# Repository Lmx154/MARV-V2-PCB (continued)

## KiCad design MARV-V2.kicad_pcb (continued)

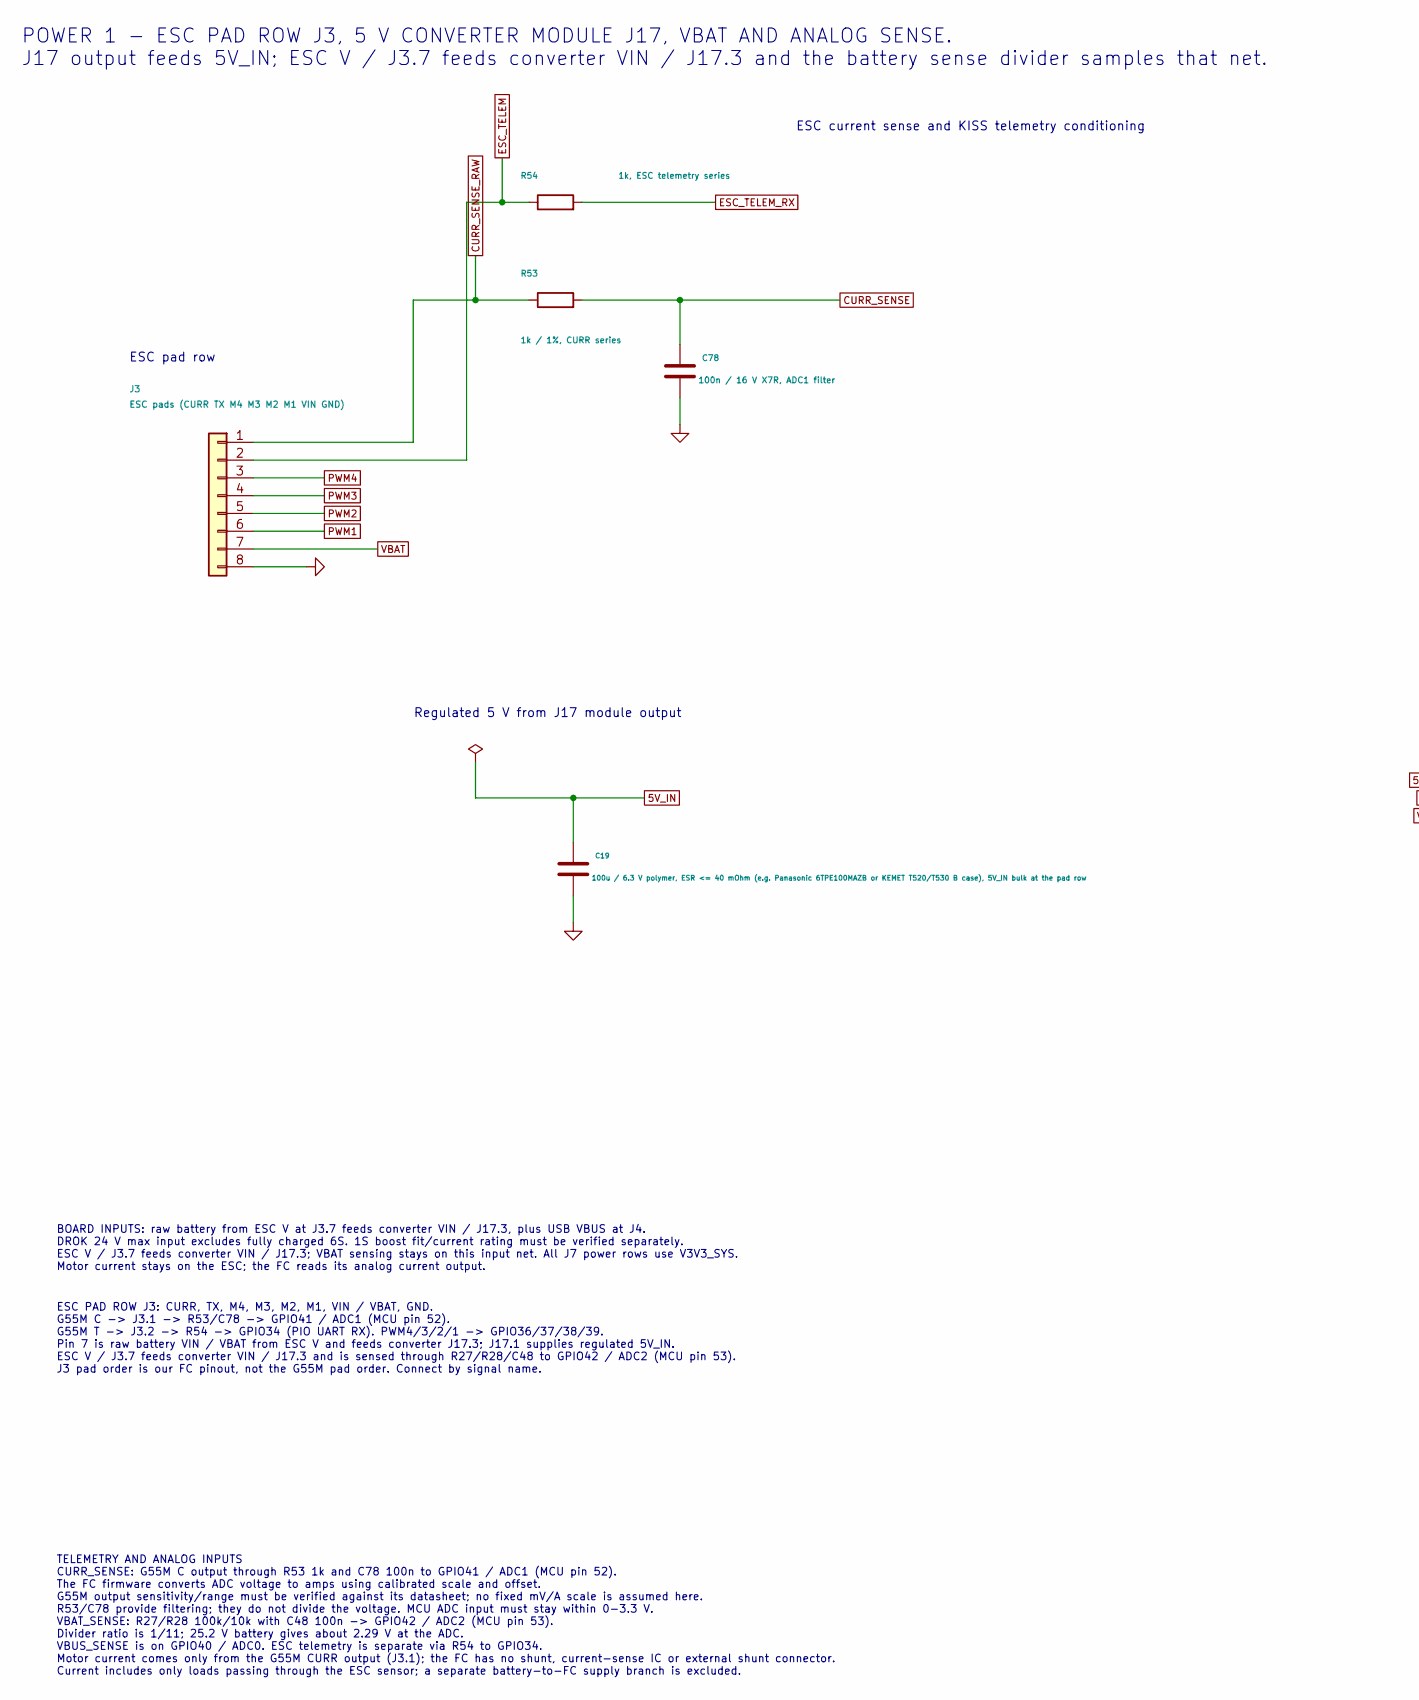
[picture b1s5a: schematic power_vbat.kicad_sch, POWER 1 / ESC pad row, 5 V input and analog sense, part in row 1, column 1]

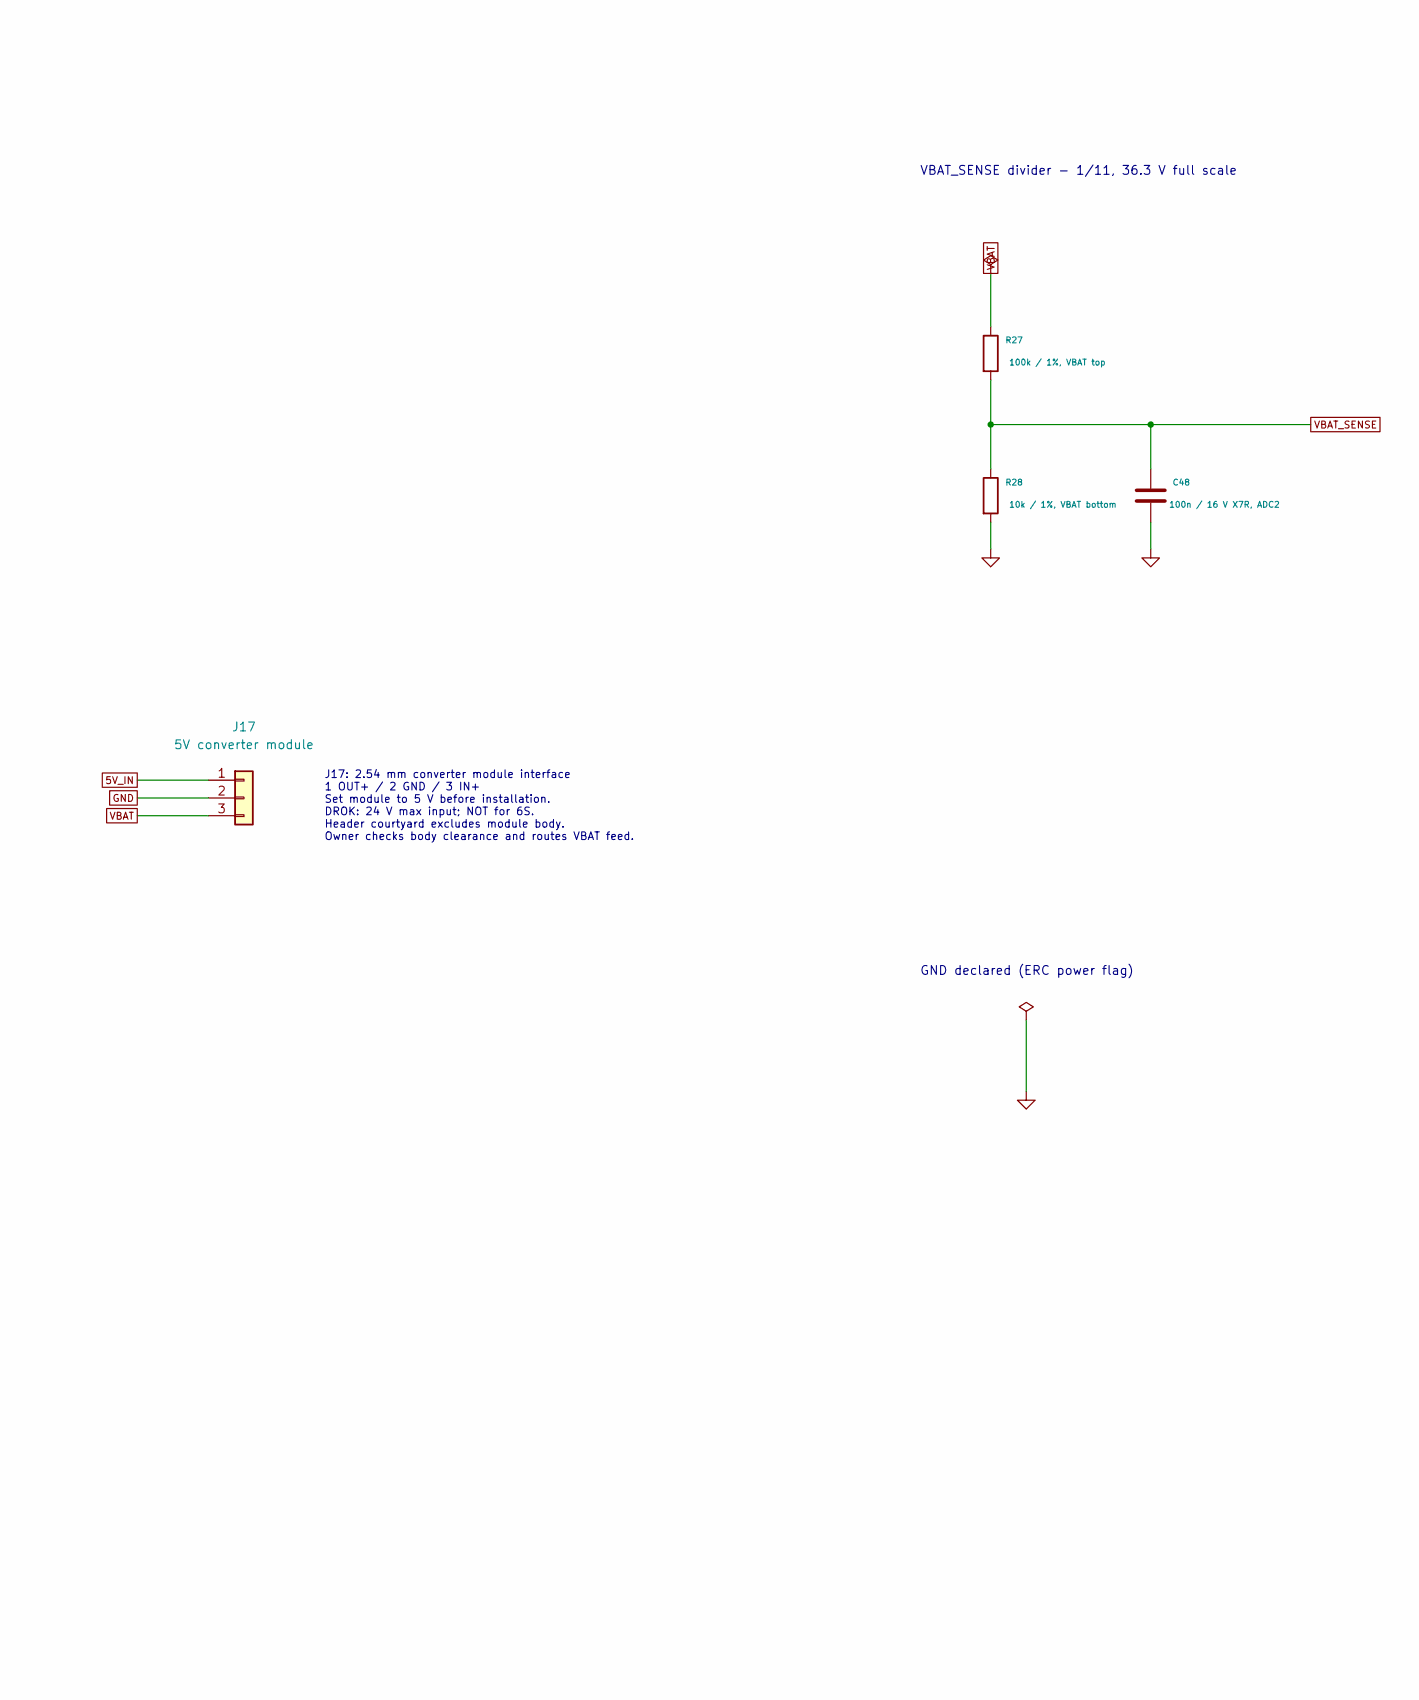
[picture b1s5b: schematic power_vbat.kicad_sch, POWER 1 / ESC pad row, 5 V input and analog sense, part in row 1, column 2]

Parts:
C19: 100u / 6.3 V polymer, ESR <= 40 mOhm (e.g. Panaso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; CP_EIA-3528-21_Kemet-B; LCSC C79109
C48: 100n / 16 V X7R, ADC2; C_0402_1005Metric; LCSC C1525
C78: 100n / 16 V X7R, ADC1 filter; C_0402_1005Metric; LCSC C1525
J3: ESC pads (CURR TX M4 M3 M2 M1 VIN GND); PadRow_1x08_P2.00mm
J17: 5V converter module; PinHeader_1x03_P2.54mm_Vertical
R27: 100k / 1%, VBAT top; R_0402_1005Metric; LCSC C25741
R28: 10k / 1%, VBAT bottom; R_0402_1005Metric; LCSC C25744
R53: 1k / 1%, CURR series; R_0402_1005Metric; LCSC C11702
R54: 1k, ESC telemetry series; R_0402_1005Metric; LCSC C11702

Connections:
5V_IN: C19.1, J17.1; also elsewhere on the board
CURR_SENSE: C78.1, R53.2; also elsewhere on the board
CURR_SENSE_RAW: J3.1, R53.1
ESC_TELEM: J3.2, R54.1
ESC_TELEM_RX: R54.2; also elsewhere on the board
GND: C19.2, C48.2, C78.2, J3.8, J17.2, R28.2; also elsewhere on the board
PWM1: J3.6; also elsewhere on the board
PWM2: J3.5; also elsewhere on the board
PWM3: J3.4; also elsewhere on the board
PWM4: J3.3; also elsewhere on the board
VBAT: J3.7, J17.3, R27.1
VBAT_SENSE: C48.1, R27.2, R28.1; also elsewhere on the board

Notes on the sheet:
ESC PAD ROW J3: CURR, TX, M4, M3, M2, M1, VIN / VBAT, GND. G55M C -> J3.1 -> R53/C78 -> GPIO41 / ADC1 (MCU pin 52). G55M T -> J3.2 -> R54 -> GPIO34 (PIO UART RX). PWM4/3/2/1 -> GPIO36/37/38/39. Pin 7 is raw battery VIN / VBAT from ESC V and feeds converter J17.3; J17.1 supplies regulated 5V_IN. ESC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
BOARD INPUTS: raw battery from ESC V at J3.7 feeds converter VIN / J17.3, plus USB VBUS at J4. DROK 24 V max input excludes fully charged 6S. 1S boost fit/current rating must be verified separately. ESC V / J3.7 feeds converter VIN / J17.3; VBAT sensing stays on this input net. All J7 power rows us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
POWER 1 - ESC PAD ROW J3, 5 V CONVERTER MODULE J17, VBAT AND ANALOG SENSE. J17 output feeds 5V_IN; ESC V / J3.7 feeds converter VIN / J17.3 and the battery sense divider samples that net.
ESC current sense and KISS telemetry conditioning
ESC pad row
Regulated 5 V from J17 module output
TELEMETRY AND ANALOG INPUTS CURR_SENSE: G55M C output through R53 1k and C78 100n to GPIO41 / ADC1 (MCU pin 52). The FC firmware converts ADC voltage to amps using calibrated scale and offset. G55M output sensitivity/range must be verified against its datasheet; no fixed mV/A scale is assumed here.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
GND declared (ERC power flag)
VBAT_SENSE divider - 1/11, 36.3 V full scale
J17: 2.54 mm converter module interface 1 OUT+ / 2 GND / 3 IN+ Set module to 5 V before installation. DROK: 24 V max input; NOT for 6S. Header courtyard excludes module body. Owner checks body clearance and routes VBAT feed.

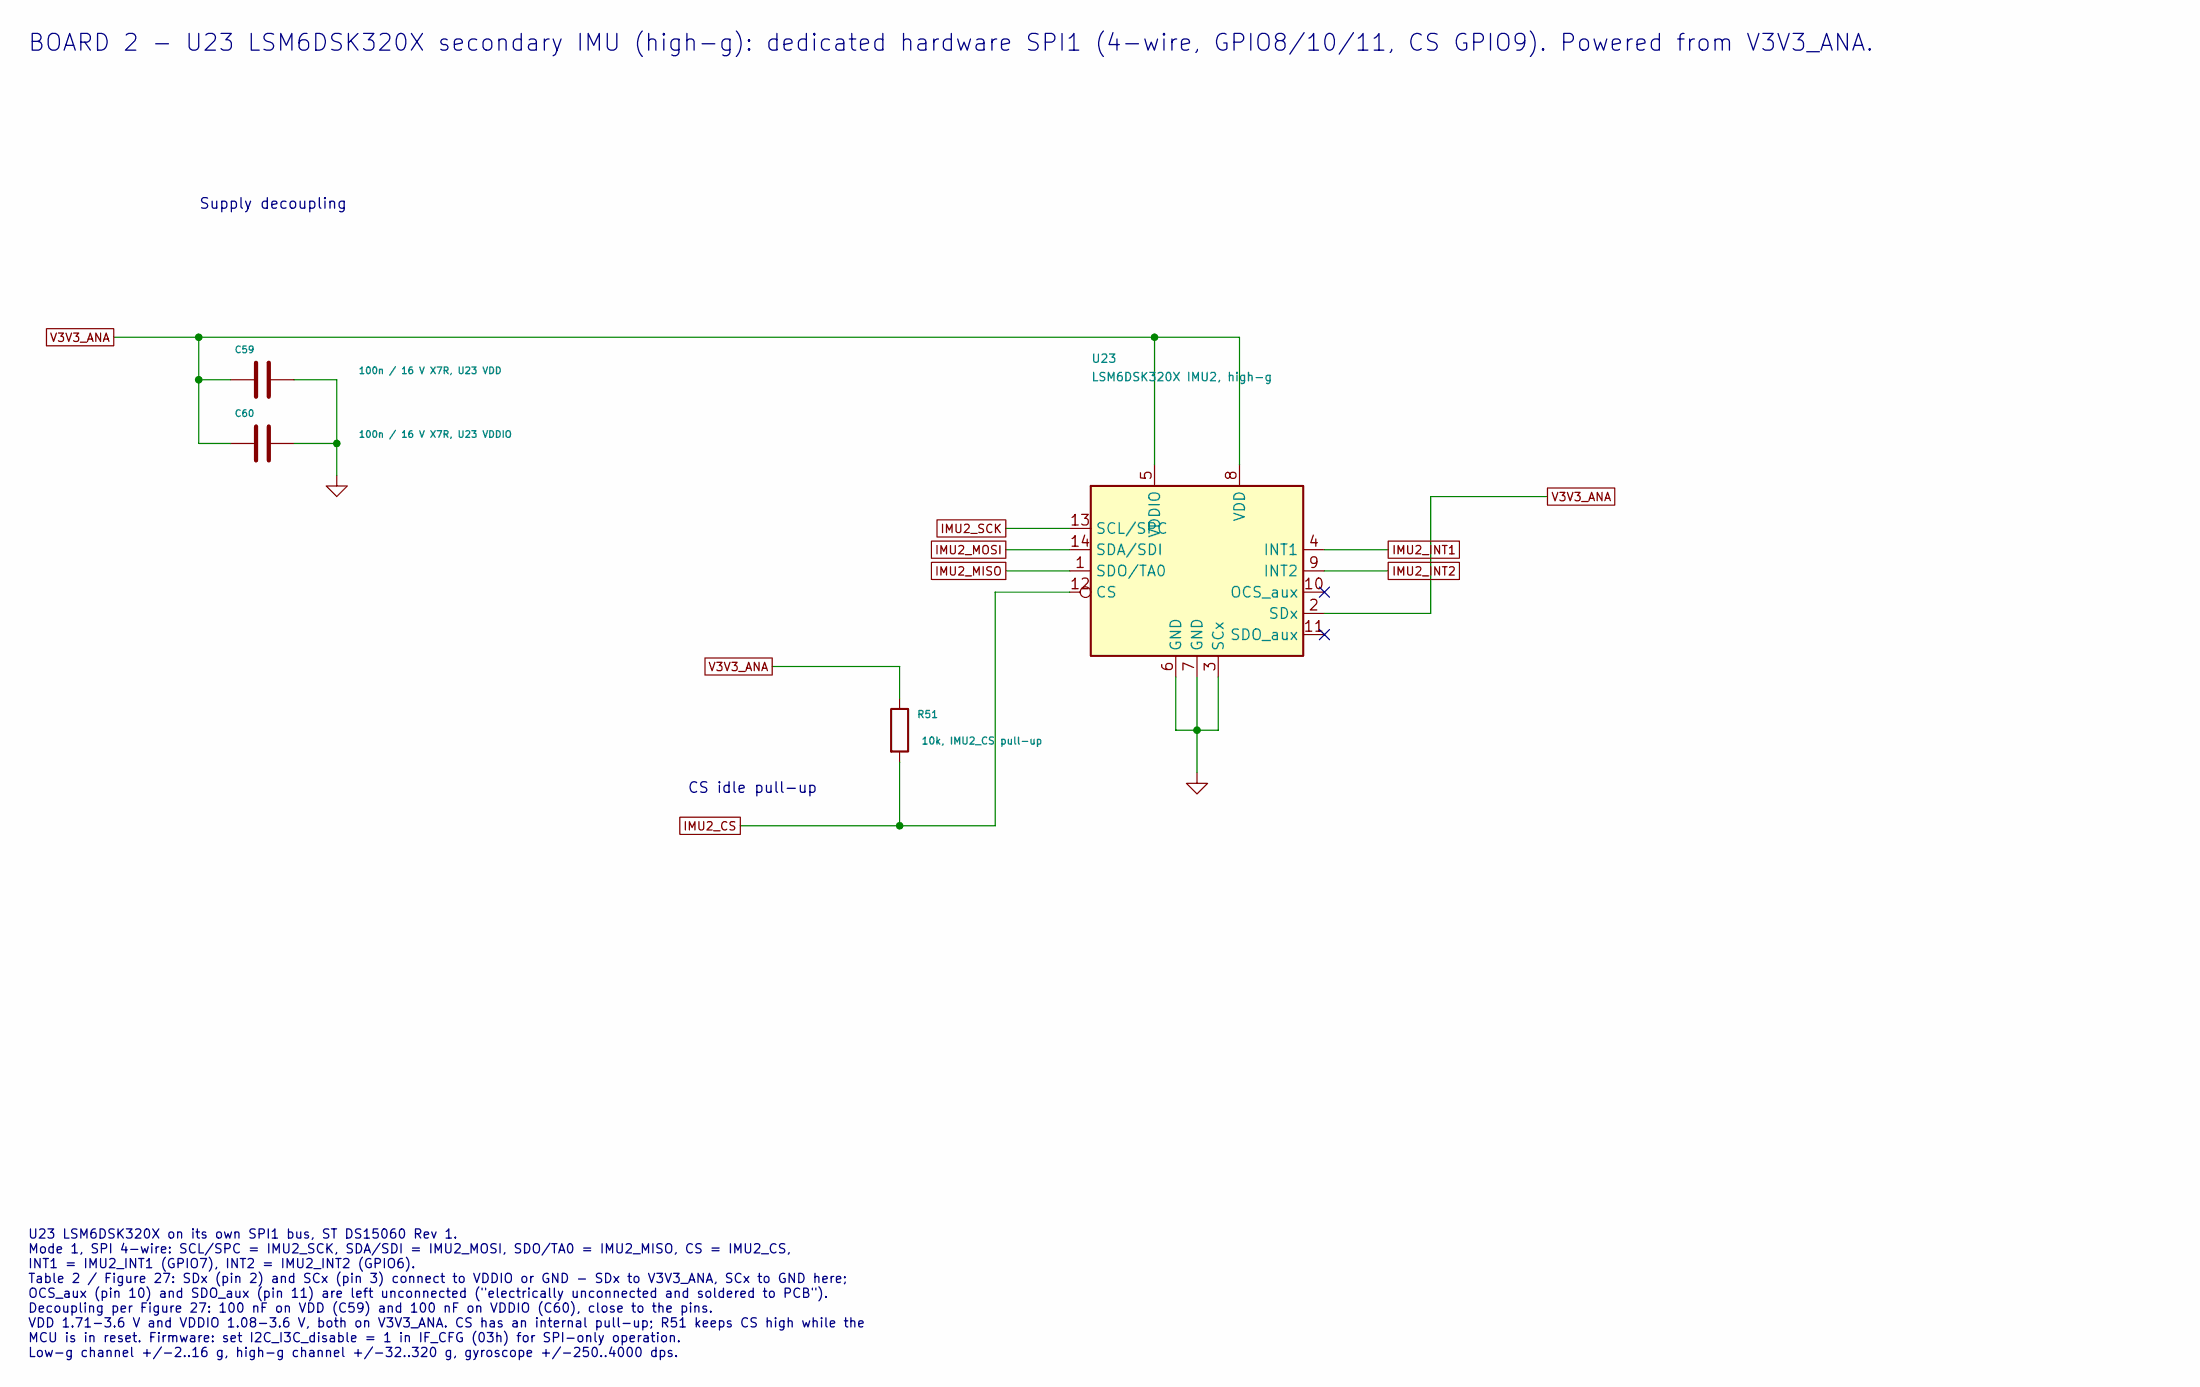
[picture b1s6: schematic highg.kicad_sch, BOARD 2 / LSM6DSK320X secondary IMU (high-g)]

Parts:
C59: 100n / 16 V X7R, U23 VDD; C_0402_1005Metric; LCSC C1525
C60: 100n / 16 V X7R, U23 VDDIO; C_0402_1005Metric; LCSC C1525
R51: 10k, IMU2_CS pull-up; R_0402_1005Metric; LCSC C25744
U23: LSM6DSK320X IMU2, high-g; ST_LGA-14_2.5x3mm_P0.5mm_LSM6DSK320X; LCSC C53025794

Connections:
GND: C59.2, C60.2, U23.3 (SCx), U23.6 (GND), U23.7 (GND); also elsewhere on the board
IMU2_CS: R51.2, U23.12 (CS); also elsewhere on the board
IMU2_INT1: U23.4 (INT1); also elsewhere on the board
IMU2_INT2: U23.9 (INT2); also elsewhere on the board
IMU2_MISO: U23.1 (SDO/TA0); also elsewhere on the board
IMU2_MOSI: U23.14 (SDA/SDI); also elsewhere on the board
IMU2_SCK: U23.13 (SCL/SPC); also elsewhere on the board
V3V3_ANA: C59.1, C60.1, R51.1, U23.2 (SDx), U23.5 (VDDIO), U23.8 (VDD); also elsewhere on the board

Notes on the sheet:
CS idle pull-up
Supply decoupling
BOARD 2 - U23 LSM6DSK320X secondary IMU (high-g): dedicated hardware SPI1 (4-wire, GPIO8/10/11, CS GPIO9). Powered from V3V3_ANA.
U23 LSM6DSK320X on its own SPI1 bus, ST DS15060 Rev 1. Mode 1, SPI 4-wire: SCL/SPC = IMU2_SCK, SDA/SDI = IMU2_MOSI, SDO/TA0 = IMU2_MISO, CS = IMU2_CS, INT1 = IMU2_INT1 (GPIO7), INT2 = IMU2_INT2 (GPIO6). Table 2 / Figure 27: SDx (pin 2) and SCx (pin 3) connect to VDDIO or GND - SDx to V3V3_ANA, SCx 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

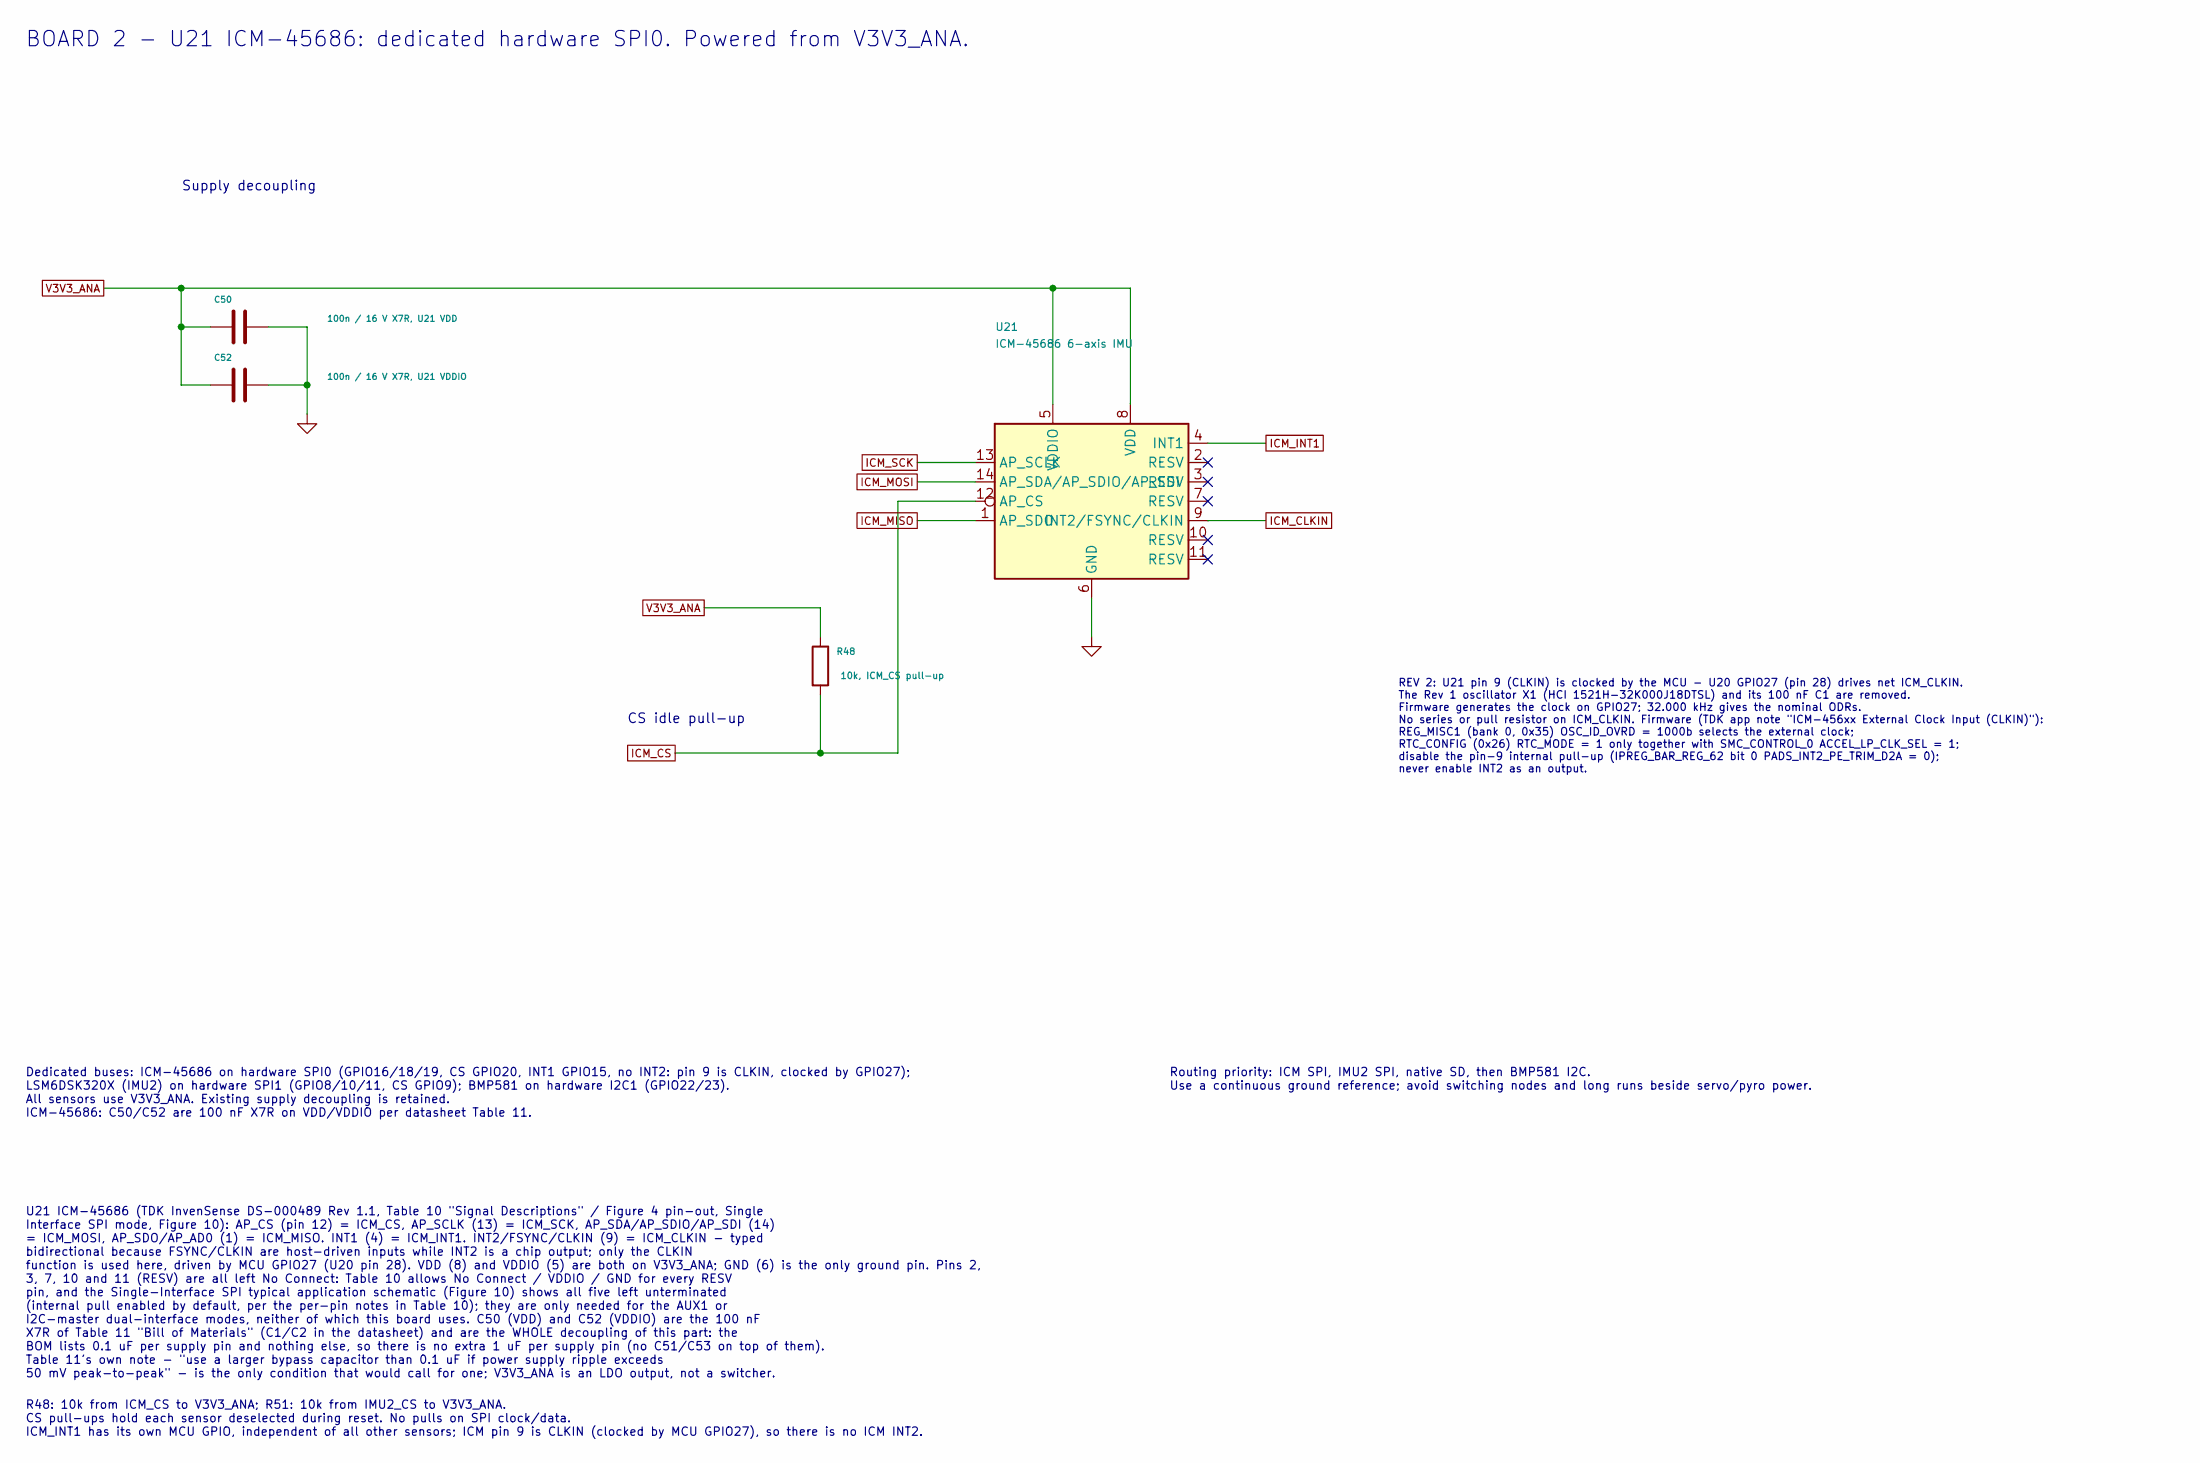
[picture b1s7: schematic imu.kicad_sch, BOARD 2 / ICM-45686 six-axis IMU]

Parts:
C50: 100n / 16 V X7R, U21 VDD; C_0402_1005Metric; LCSC C1525
C52: 100n / 16 V X7R, U21 VDDIO; C_0402_1005Metric; LCSC C1525
R48: 10k, ICM_CS pull-up; R_0402_1005Metric; LCSC C25744
U21: ICM-45686 6-axis IMU; InvenSense_LGA-14_2.5x3mm_P0.5mm_ICM45686; LCSC C22459454

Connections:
GND: C50.2, C52.2, U21.6 (GND); also elsewhere on the board
ICM_CLKIN: U21.9 (INT2/FSYNC/CLKIN); also elsewhere on the board
ICM_CS: R48.2, U21.12 (AP_CS); also elsewhere on the board
ICM_INT1: U21.4 (INT1); also elsewhere on the board
ICM_MISO: U21.1 (AP_SDO); also elsewhere on the board
ICM_MOSI: U21.14 (AP_SDA/AP_SDIO/AP_SDI); also elsewhere on the board
ICM_SCK: U21.13 (AP_SCLK); also elsewhere on the board
V3V3_ANA: C50.1, C52.1, R48.1, U21.5 (VDDIO), U21.8 (VDD); also elsewhere on the board

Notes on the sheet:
Supply decoupling
Dedicated buses: ICM-45686 on hardware SPI0 (GPIO16/18/19, CS GPIO20, INT1 GPIO15, no INT2: pin 9 is CLKIN, clocked by GPIO27); LSM6DSK320X (IMU2) on hardware SPI1 (GPIO8/10/11, CS GPIO9); BMP581 on hardware I2C1 (GPIO22/23). All sensors use V3V3_ANA. Existing supply decoupling is retained. ICM-456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
U21 ICM-45686 (TDK InvenSense DS-000489 Rev 1.1, Table 10 "Signal Descriptions" / Figure 4 pin-out, Single Interface SPI mode, Figure 10): AP_CS (pin 12) = ICM_CS, AP_SCLK (13) = ICM_SCK, AP_SDA/AP_SDIO/AP_SDI (14) = ICM_MOSI, AP_SDO/AP_AD0 (1) = ICM_MISO. INT1 (4) = ICM_INT1. INT2/FSYNC/CLKIN (9) 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
R48: 10k from ICM_CS to V3V3_ANA; R51: 10k from IMU2_CS to V3V3_ANA. CS pull-ups hold each sensor deselected during reset. No pulls on SPI clock/data. ICM_INT1 has its own MCU GPIO, independent of all other sensors; ICM pin 9 is CLKIN (clocked by MCU GPIO27), so there is no ICM INT2.
Routing priority: ICM SPI, IMU2 SPI, native SD, then BMP581 I2C. Use a continuous ground reference; avoid switching nodes and long runs beside servo/pyro power.
BOARD 2 - U21 ICM-45686: dedicated hardware SPI0. Powered from V3V3_ANA.
REV 2: U21 pin 9 (CLKIN) is clocked by the MCU - U20 GPIO27 (pin 28) drives net ICM_CLKIN. The Rev 1 oscillator X1 (HCI 1521H-32K000J18DTSL) and its 100 nF C1 are removed. Firmware generates the clock on GPIO27; 32.000 kHz gives the nominal ODRs. No series or pull resistor on ICM_CLKIN. Firmware (T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
CS idle pull-up

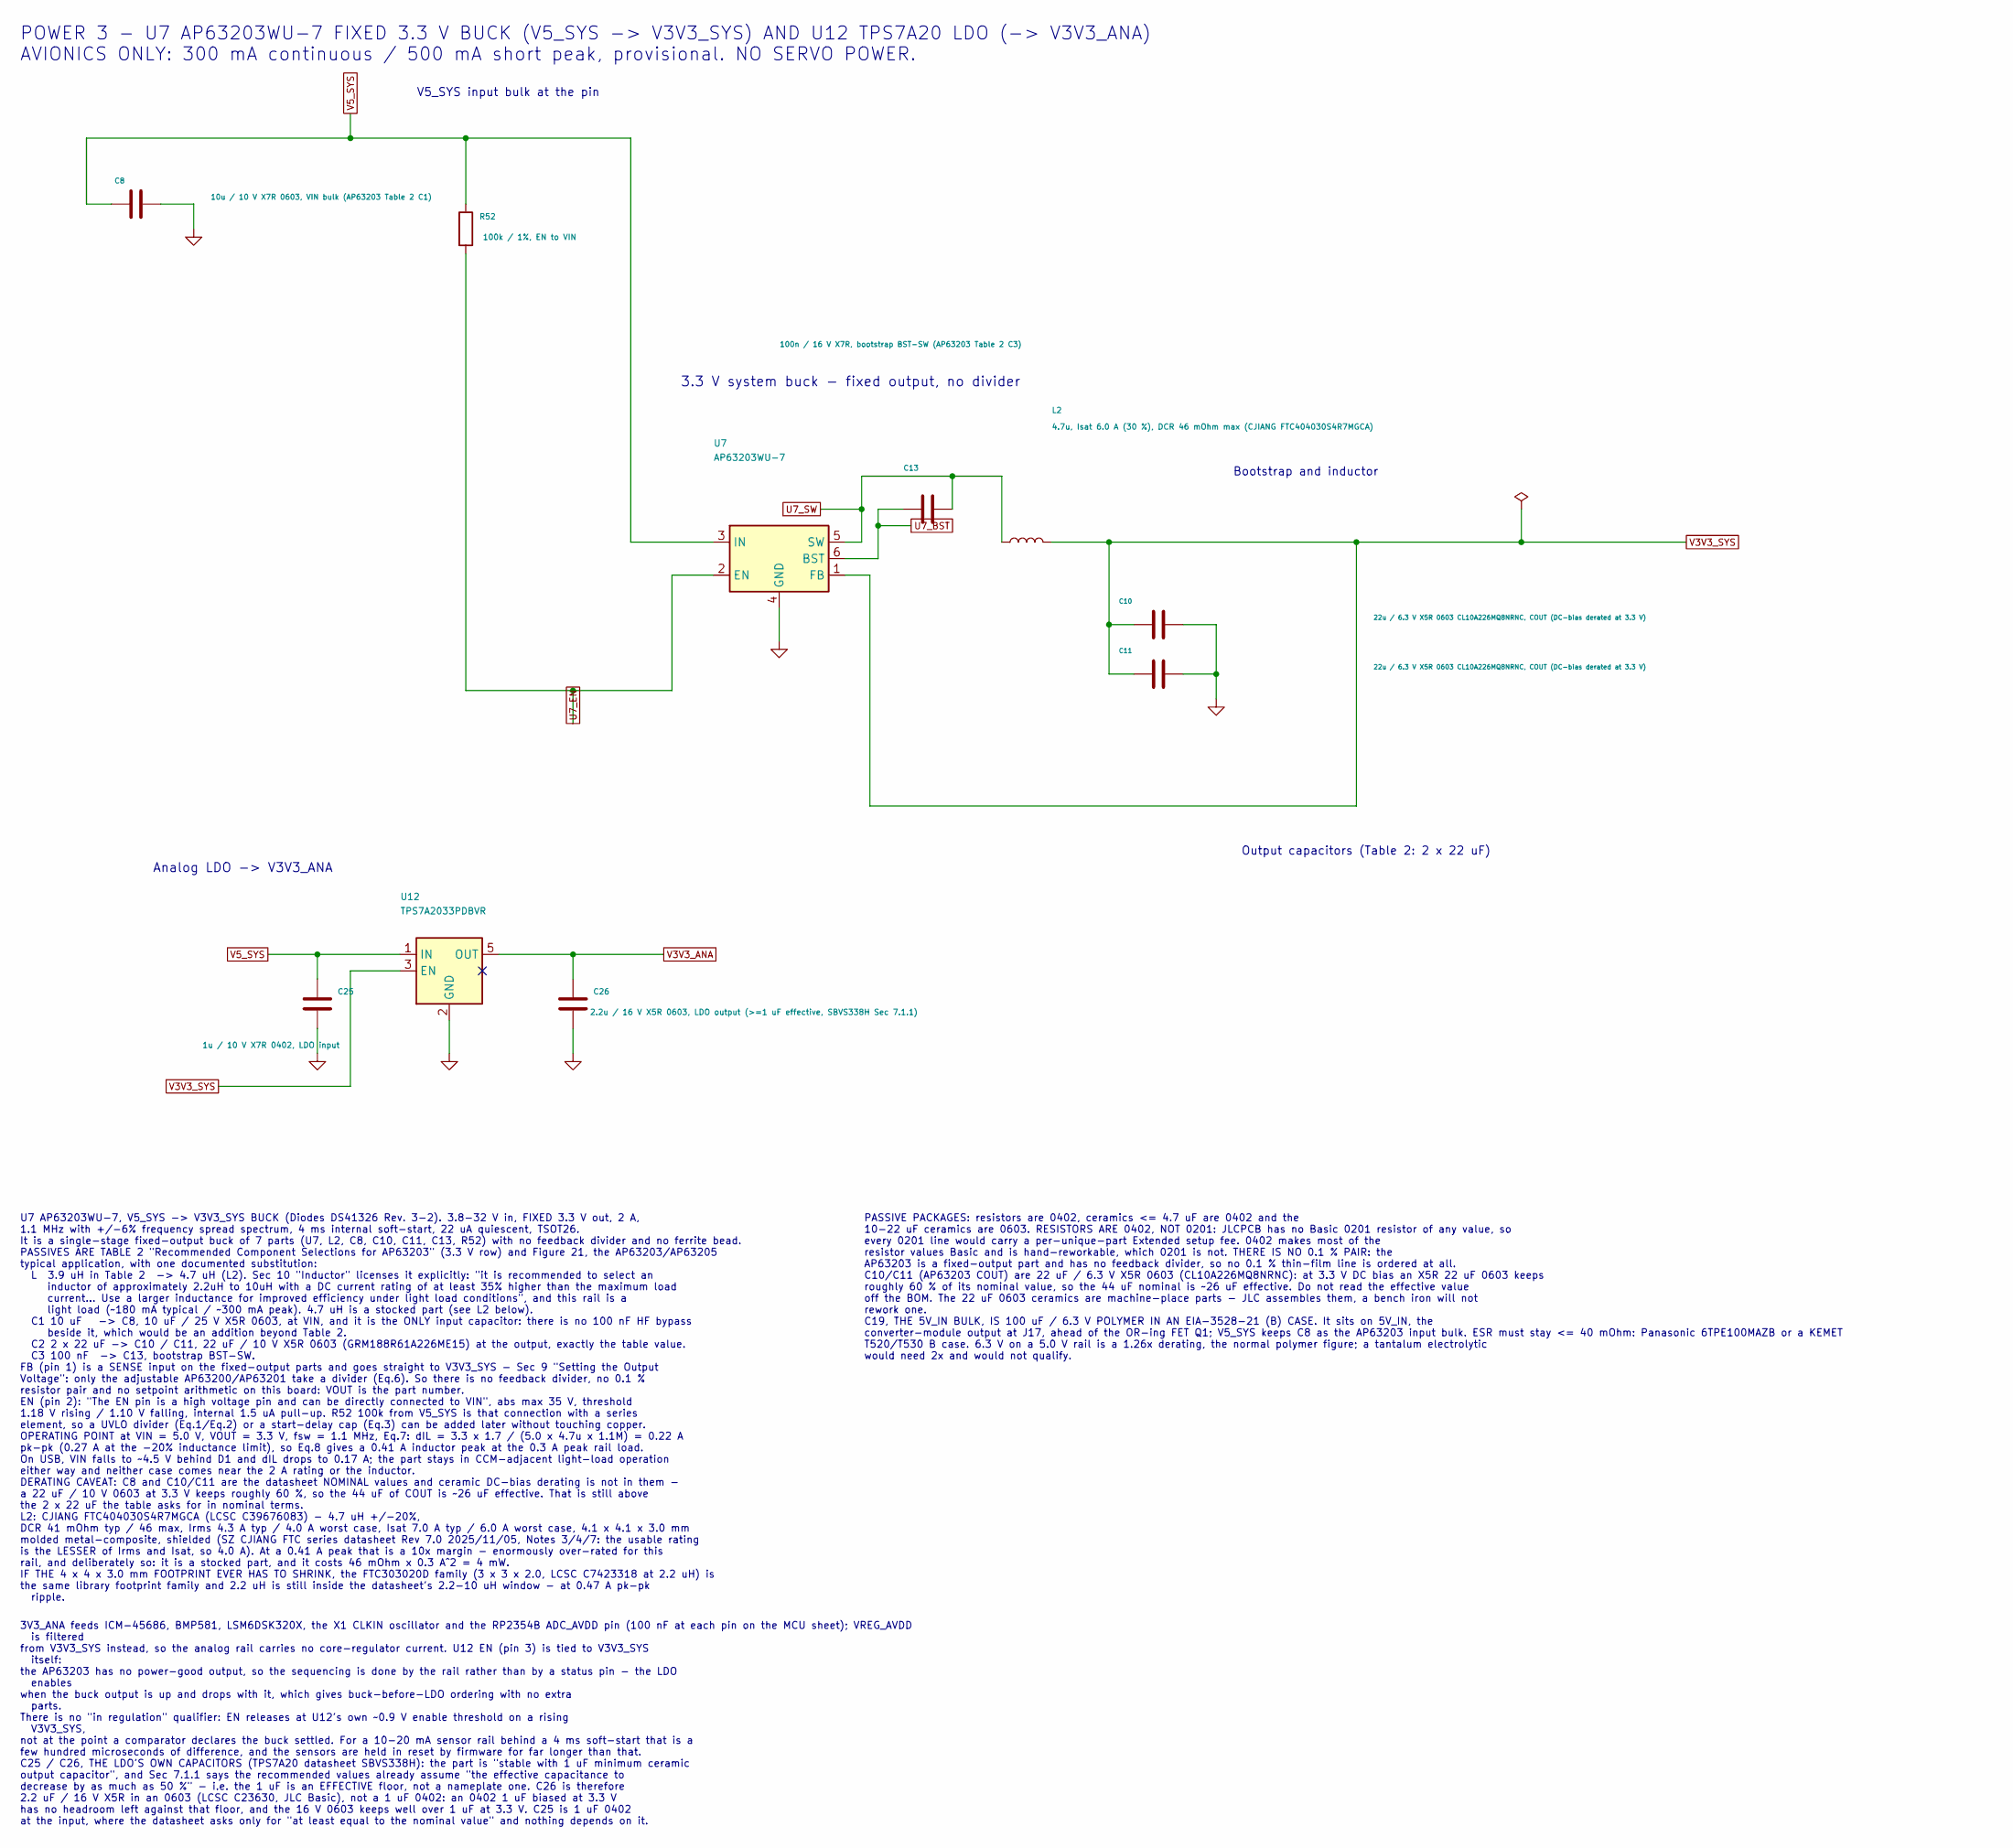
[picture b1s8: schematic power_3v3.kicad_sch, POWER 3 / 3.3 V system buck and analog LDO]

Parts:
C8: 10u / 10 V X7R 0603, VIN bulk (AP63203 Table 2 C1); C_0603_1608Metric; LCSC C96446
C10, C11: 22u / 6.3 V X5R 0603 CL10A226MQ8NRNC, COUT (DC-bi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; C_0603_1608Metric; LCSC C59461
C13: 100n / 16 V X7R, bootstrap BST-SW (AP63203 Table 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; C_0402_1005Metric; LCSC C1525
C25: 1u / 10 V X7R 0402, LDO input; C_0402_1005Metric; LCSC C52923
C26: 2.2u / 16 V X5R 0603, LDO output (>=1 uF effectiv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; C_0603_1608Metric; LCSC C23630
L2: 4.7u, Isat 6.0 A (30 %), DCR 46 mOhm max (CJIANG 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; L_Changjiang_FTC404030S; LCSC C39676083
R52: 100k / 1%, EN to VIN; R_0402_1005Metric; LCSC C25741
U7: AP63203WU-7; TSOT-23-6; LCSC C780769
U12: TPS7A2033PDBVR; SOT-23-5; LCSC C2862740

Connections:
GND: C8.2, C10.2, C11.2, C25.2, C26.2, U7.4 (GND), U12.2 (GND); also elsewhere on the board
U7_BST: C13.1, U7.6 (BST)
U7_EN: R52.2, U7.2 (EN)
U7_SW: C13.2, L2.1, U7.5 (SW)
V3V3_ANA: C26.1, U12.5 (OUT); also elsewhere on the board
V3V3_SYS: C10.1, C11.1, L2.2, U7.1 (FB), U12.3 (EN); also elsewhere on the board
V5_SYS: C8.1, C25.1, R52.1, U7.3 (IN), U12.1 (IN); also elsewhere on the board

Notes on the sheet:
POWER 3 - U7 AP63203WU-7 FIXED 3.3 V BUCK (V5_SYS -> V3V3_SYS) AND U12 TPS7A20 LDO (-> V3V3_ANA) AVIONICS ONLY: 300 mA continuous / 500 mA short peak, provisional. NO SERVO POWER.
3.3 V system buck - fixed output, no divider
Bootstrap and inductor
V5_SYS input bulk at the pin
Analog LDO -> V3V3_ANA
U7 AP63203WU-7, V5_SYS -> V3V3_SYS BUCK (Diodes DS41326 Rev. 3-2). 3.8-32 V in, FIXED 3.3 V out, 2 A, 1.1 MHz with +/-6% frequency spread spectrum, 4 ms internal soft-start, 22 uA quiescent, TSOT26. It is a single-stage fixed-output buck of 7 parts (U7, L2, C8, C10, C11, C13, R52) with no feedback 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
PASSIVE PACKAGES: resistors are 0402, ceramics <= 4.7 uF are 0402 and the 10-22 uF ceramics are 0603. RESISTORS ARE 0402, NOT 0201: JLCPCB has no Basic 0201 resistor of any value, so every 0201 line would carry a per-unique-part Extended setup fee. 0402 makes most of the resistor values Basic and i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
3V3_ANA feeds ICM-45686, BMP581, LSM6DSK320X, the X1 CLKIN oscillator and the RP2354B ADC_AVDD pin (100 nF at each pin on the MCU sheet); VREG_AVDD is filtered from V3V3_SYS instead, so the analog rail carries no core-regulator current. U12 EN (pin 3) is tied to V3V3_SYS itself: the AP63203 has no 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
Output capacitors (Table 2: 2 x 22 uF)

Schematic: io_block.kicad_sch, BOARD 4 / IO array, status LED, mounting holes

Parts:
C79: 100n / 16 V X7R, D20 VDD; C_0402_1005Metric; LCSC C1525
D20: WS2812C-2020 RGB; LED_WS2812B-2020_PLCC4_2.0x2.0mm; LCSC C55109522
H1, H2, H3, H4: M3 grommet hole, 4.0 mm, GND ring; MountingHole_4.0mm_Grommet_Pad_Via
J6: IO array signal column (innermost); PinHeader_1x14_P2.54mm_Vertical_IORow; LCSC C2905490
J7: IO array power column (5V / 3V3 per row); PinHeader_1x14_P2.54mm_Vertical_IORow; LCSC C2905490
J8: IO array GND column (board edge); PinHeader_1x14_P2.54mm_Vertical_IORow; LCSC C2905490
R55: 100 / 1%, WS2812 data series; R_0402_1005Metric; LCSC C25076

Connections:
ELRS_RX: J6.1; also elsewhere on the board
ELRS_TX: J6.2; also elsewhere on the board
GND: C79.2, D20.2 (VSS), H1.1 (1_1), H2.1 (1_1), H3.1 (1_1), H4.1 (1_1), J8.1, J8.2, J8.3, J8.4, J8.5, J8.6, J8.7, J8.8, J8.9, J8.10, J8.11, J8.12, J8.13, J8.14; also elsewhere on the board
GPS_RX: J6.3; also elsewhere on the board
GPS_TX: J6.4; also elsewhere on the board
IO_GPIO44: J6.11; also elsewhere on the board
IO_GPIO45: J6.12; also elsewhere on the board
IO_GPIO46: J6.13; also elsewhere on the board
IO_GPIO47: J6.14; also elsewhere on the board
LED_DATA: R55.1; also elsewhere on the board
LED_DIN: D20.3 (DIN), R55.2
MAG_SCL: J6.6; also elsewhere on the board
MAG_SDA: J6.5; also elsewhere on the board
PWM5: J6.7; also elsewhere on the board
PWM6: J6.8; also elsewhere on the board
PWM7: J6.9; also elsewhere on the board
PWM8: J6.10; also elsewhere on the board
V3V3_SYS: J7.1, J7.2, J7.3, J7.4, J7.5, J7.6, J7.7, J7.8, J7.9, J7.10, J7.11, J7.12, J7.13, J7.14; also elsewhere on the board
V5_SYS: C79.1, D20.4 (VDD); also elsewhere on the board

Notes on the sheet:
IO ARRAY - ONE 3-COLUMN x 14-ROW THROUGH-HOLE BLOCK ON THE RIGHT EDGE, 2.54 mm, madflight FC3v2 style. It is the only IO block - there is no separate edge array and no servo connector block: every signal that leaves this board except the ESC row (J3) and the SWD header (J10) leaves on this one bloc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
WS2812C status LED
Mechanical
IO array - one row per module lead
BOARD 4 - THE 3 x 14 IO BLOCK (J6 SIGNAL / J7 POWER / J8 GND), THE WS2812C STATUS LED AND THE FOUR M3 GROMMET HOLES. Every signal that leaves the board except the ESC row J3 and the SWD header J10 leaves here.
PWM2 = GPIO38 PWM3 = GPIO37 PWM4 = GPIO36
RAILS ON THE ARRAY: rows 1-6 (GPS, ELRS, magnetometer) and rows 11-14 take V3V3_SYS; rows 7-10 (S5-S8 signal rows) take V3V3_SYS as well. Every row has its own GND pin in the J8 column, so a signal return is never more than 2.54 mm away and no row can be mis-plugged into a neighbour's ground. ROWS 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
IO ARRAY ROW MAP (row n = J6 pin n signal | J7 pin n power | J8 pin n GND) 1 T1 ELRS_RX | V3V3_SYS | GND UART1 TX -> ELRS RX (GPIO24) 2 R1 ELRS_TX | V3V3_SYS | GND UART1 RX <- ELRS TX (GPIO25) 3 T0 GPS_RX | V3V3_SYS | GND UART0 TX (F11) -> GPS RX (GPIO14) 4 R0 GPS_TX | V3V3_SYS | GND UART0 RX (F2) 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
MECHANICAL: H1-H4 are the four 4.0 mm grommet holes on the standard 30.5 x 30.5 mm pattern, off-centre in X, each a PLATED hole with a 6.4 mm GND pad ring stitched by eight 0.6/0.3 mm vias, and a 6.5 mm top-side courtyard for the grommet flange. Pin 1 of every hole is GND, so the frame screws bond 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
PWM MAP PWM5 = GPIO5 (row 7, S5) PWM6 = GPIO4 (row 8, S6) PWM7 = GPIO3 (row 9, S7) PWM8 = GPIO2 (row 10, S8) ON THE ESC PAD ROW (J3, POWER 1) PWM1 = GPIO39

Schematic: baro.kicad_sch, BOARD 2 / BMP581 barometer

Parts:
C54: 100n / 16 V X7R, U22 VDD; C_0402_1005Metric; LCSC C1525
C56: 100n / 16 V X7R, U22 VDDIO; C_0402_1005Metric; LCSC C1525
R50, R57: 4.7k; R_0402_1005Metric; LCSC C25900
U22: BMP581 barometer; Bosch_LGA-10_2x2mm_BMP581; LCSC C5362283

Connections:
BARO_INT: U22.7 (INT); also elsewhere on the board
BARO_SCL: R50.2, U22.2 (SCL); also elsewhere on the board
BARO_SDA: R57.2, U22.4 (SDA); also elsewhere on the board
GND: C54.2, C56.2, U22.3 (VSS), U22.5 (ADDR/SDO), U22.8 (VSS), U22.9 (VSS); also elsewhere on the board
V3V3_ANA: C54.1, C56.1, R50.1, R57.1, U22.1 (VDDIO), U22.6 (CSB), U22.10 (VDD); also elsewhere on the board

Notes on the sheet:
Supply decoupling
U22 BMP581: SCK/SCL = BARO_SCL; SDI/SDA = BARO_SDA; INT = BARO_INT (dedicated GPIO21); SDA/SCL on I2C1 GPIO22/23. CSB is hard-wired to VDDIO / V3V3_ANA for I2C mode. SDO/ADDR is tied to GND: 7-bit address 0x46. R50 and R57 are 4.7k pull-ups to V3V3_ANA on SCL and SDA; no pull-downs. VDDIO and VDD u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
BOARD 2 - U22 BMP581 BAROMETER: hardware I2C1 (GPIO22/23), powered from V3V3_ANA.
I2C pull-ups: 4.7k

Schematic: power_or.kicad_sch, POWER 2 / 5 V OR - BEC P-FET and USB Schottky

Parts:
D1: 1N5819WS; D_SOD-323; LCSC C191023
Q1: AO3401A; SOT-23; LCSC C15127
R7: 100k / 1%, Q1 gate pull-down; R_0402_1005Metric; LCSC C25741

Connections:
5V_IN: Q1.3 (D); also elsewhere on the board
GND: R7.2; also elsewhere on the board
USB_VBUS: D1.2 (A), Q1.1 (G), R7.1; also elsewhere on the board
V5_SYS: D1.1 (K), Q1.2 (S); also elsewhere on the board

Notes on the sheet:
Gate on USB_VBUS - USB present = Q1 off
USB path - D1 Schottky, the only way USB reaches V5_SYS
BEC path - Q1 P-channel FET, drain 5V_IN, source V5_SYS
5 V INPUT OR: Q1 AO3401A and D1 1N5819WS. Q1 drain = 5V_IN, source = V5_SYS, gate = USB_VBUS. R7 pulls the gate down. D1 anode = USB_VBUS; cathode = V5_SYS. Without USB, Q1's channel carries the external supply after its gate discharges. With USB present, Q1 can be off: D1 and Q1's body diode can s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
POWER 2 - Q1 AO3401A P-FET + D1 1N5819WS SCHOTTKY. 5V_IN (regulated converter output, J17 pin 1) OR USB_VBUS -> V5_SYS. USB present turns Q1 OFF, so a host can never back-feed the BEC, the servo rows or the ESC.
V5_SYS - the two 3.3 V regulators and the status LED, nothing else
USB_VBUS feeds the D1 Schottky and the Q1 gate on POWER 2 directly; no inrush or current limiting on this sheet, and no data ESD array - a USBLC6-2SC6 is JLC Extended and is not fitted, so D+/D- go straight from J4 into the 27 R series pair R22/R23, as on the madflight FC3v2. The RP2354B USB pins c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
